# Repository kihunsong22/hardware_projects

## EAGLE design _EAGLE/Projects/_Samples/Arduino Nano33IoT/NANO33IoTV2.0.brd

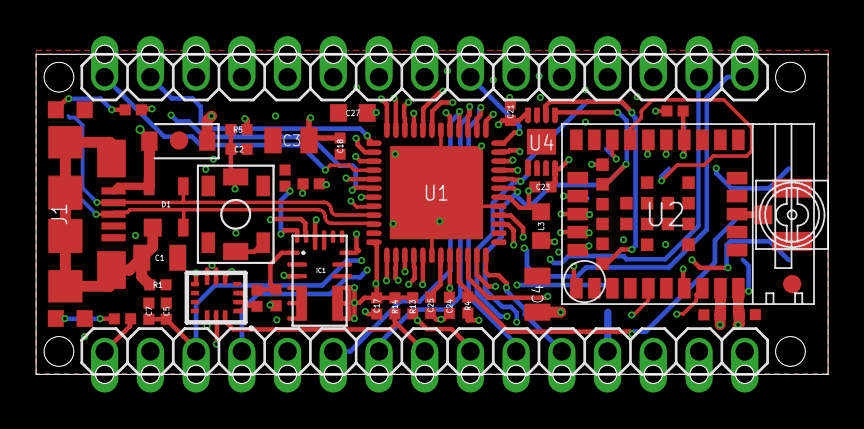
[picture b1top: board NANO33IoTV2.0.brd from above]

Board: 4 copper layers, 44.0 x 17.8 mm, 54 parts (1 on the bottom side), 51 nets.

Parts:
C1: 4n7; 0805-R2013X50N
C2, C7, C8, C9, C17, C18, C21, C23, C24: 100n; 0402-1005X55N
C3, C4: 22u; 0805-R2013X50N
C5: 4u7; 0402-1005X55N
C25: 1u; 0402-1005X55N
C27: 4u7; 0603-1608X90N
D1: PRTR5V; SOT190P230X110-4N
D2: PMEG6020; SODFL3517X110N
D+: DNP; TP-1.00MM
D-: DNP; TP-1.00MM
DL1: YELLOW; LEDC1608X80N-AK
DL2: GREEN; LEDC1608X80N-AK
FD1, FD2: DNP; FD-1-1.5
FRAME1: DNP; FRAME
IC1: MPM3610
J1: -; ZX62-AB-5PA
J3: DNP; U.FL-R-SMT-1(60)/NO_CREAM
J4: DNP; 2X03-TP1
JP2, JP3: 1X15-CASTELL
L3: BLM18PG471; 0603-1608X90N
PB1: PTS820; C&K_PTS820_NO_HOLES
R1: 1M; 0402-1005X55N
R2, R3: 330R; 0402-1005X55N
R4: 1k; 0402-1005X55N
R5, R7, R10: 100k; 0402-1005X55N
R6: 75k; 0402-1005X55N
R8: 24k; 0402-1005X55N
R9: 39k; 0402-1005X55N
R13, R14: 4k7; 0402-1005X55N
SJ1: DNP; SJ
TP_GPIO0: DNP; TP-0.8MM
TP_RST: DNP; TP-0.8MM
TP_RX: DNP; TP-0.8MM
TP_TX: DNP; TP-0.8MM
U1: D21G18; QFN50P700X700X90-49XN-EPSQ515
U2: NINA-W102; NINA-W1X
U3: LSM6DS3TR; LGA14L
U4: ECC608; SON50P300X200X60-9N-EP160X140
U$1: DNP; FRAME

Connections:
+3V3: C3.1, C8.1, C9.2, C17.1, C18.1, C21.1, C24.1, IC1.7, IC1.8, IC1.9, IC1.20, J4.1, JP2.2, L3.1, R2.2, R4.2, R5.2, R6.2, R7.2, R13.2, R14.2, U1.17, U1.36, U1.44, U2.9, U2.10, U3.5, U3.8, U3.12, U4.8
A0/DAC0: JP2.4, U1.3
A1: JP2.5, U1.47
A2: JP2.6, U1.16
A3: JP2.7, U1.15
A4/SDA: JP2.8, R14.1, U1.7, U2.35, U3.14, U4.5
A5/SCL: JP2.9, R13.1, U1.8, U2.31, U3.13, U4.6
A6: JP2.10, U1.14, U2.5
A7: JP2.11, U1.48, U2.8
AREF: C5.1, C7.1, JP2.3, U1.4
D2: JP3.5, U1.19
D3~: JP3.6, U1.20
D4: JP3.7, U1.12
D5~: JP3.8, U1.10
D6~: JP3.9, U1.9
D7: JP3.10, U1.11
D8: JP3.11, U1.27
D9~: JP3.12, U1.29
D10~: JP3.13, U1.30
GND: C1.2, C2.2, C3.2, C4.2, C5.2, C7.2, C8.2, C9.1, C17.2, C18.2, C21.2, C23.2, C24.2, C25.2, C27.2, DL1.C, DL2.C, IC1.3, IC1.12, IC1.13, IC1.14, J1.5, J3.GND1, J3.GND2, J4.5, JP2.14, JP3.4, PB1.1, PB1.2, PB1.3, PB1.4, PB1.5, R1.1, R8.1, R9.1, U1.5, U1.18, U1.35, U1.42, U1.49, U2.6, U2.12, U2.14, U2.26, U2.30, U2.GND@1, U2.GND@2, U2.GND@3, U2.GND@4, U2.GND@5, U2.GND@6, U2.GND@7, U2.GND@8, U2.GND@9, U2.GND@10, U2.GND@11, U2.GND@12, U3.1, U3.2, U3.3, U3.6, U3.7, U4.4
MISO~: JP3.15, U1.28
MOSI: JP3.14, U1.25
N17852357: C23.1, C27.1, L3.2, U1.6
N17852431: C25.1, U1.43
unnamed: C1.1, D1.1, J1.6, J1.7, J1.8, J1.9, J1.10, J1.11, R1.2
unnamed: DL2.A, R2.1
unnamed: DL1.A, R3.1
unnamed: J3.SIG, U2.13
unnamed: IC1.1, R6.1, R8.2
unnamed: IC1.18, R9.2
unnamed: IC1.17, R10.1
unnamed: JP2.12, SJ1.2
PA12_S2_TX/MOSI: U1.21, U2.36
PA13_S2_RX/MISO: U1.22, U2.1
PA14_S2_RTS/CS: U1.23, U2.21, U2.28
PA15_S2_CTS/SCK: U1.24, U2.20, U2.29
PA27_GPIO0: TP_GPIO0.X, U1.39, U2.27
PA28_ACK: U1.41, U2.7
PA30_SWCLK: J4.3, R4.1, U1.45
PA31_SWDIO: J4.2, U1.46
RESETN: C2.1, J4.6, JP2.13, JP3.3, PB1.6, R5.1, U1.40
RSTN_NINA: R7.1, TP_RST.X, U1.13, U2.19
RX: JP3.2, U1.38
RX_NINA_PROG: TP_RX.X, U1.32, U2.22
SCK: JP2.1, R3.2, U1.26
TX: JP3.1, U1.37
TX_NINA_PROG: TP_TX.X, U1.31, U2.23
USB_N: D1.3, D-.X, J1.2, U1.33
USB_P: D1.2, D+.X, J1.3, U1.34
VIN: C4.1, D2.C, IC1.16, JP2.15, R10.2
VUSB: D1.4, D2.A, J1.1, SJ1.1

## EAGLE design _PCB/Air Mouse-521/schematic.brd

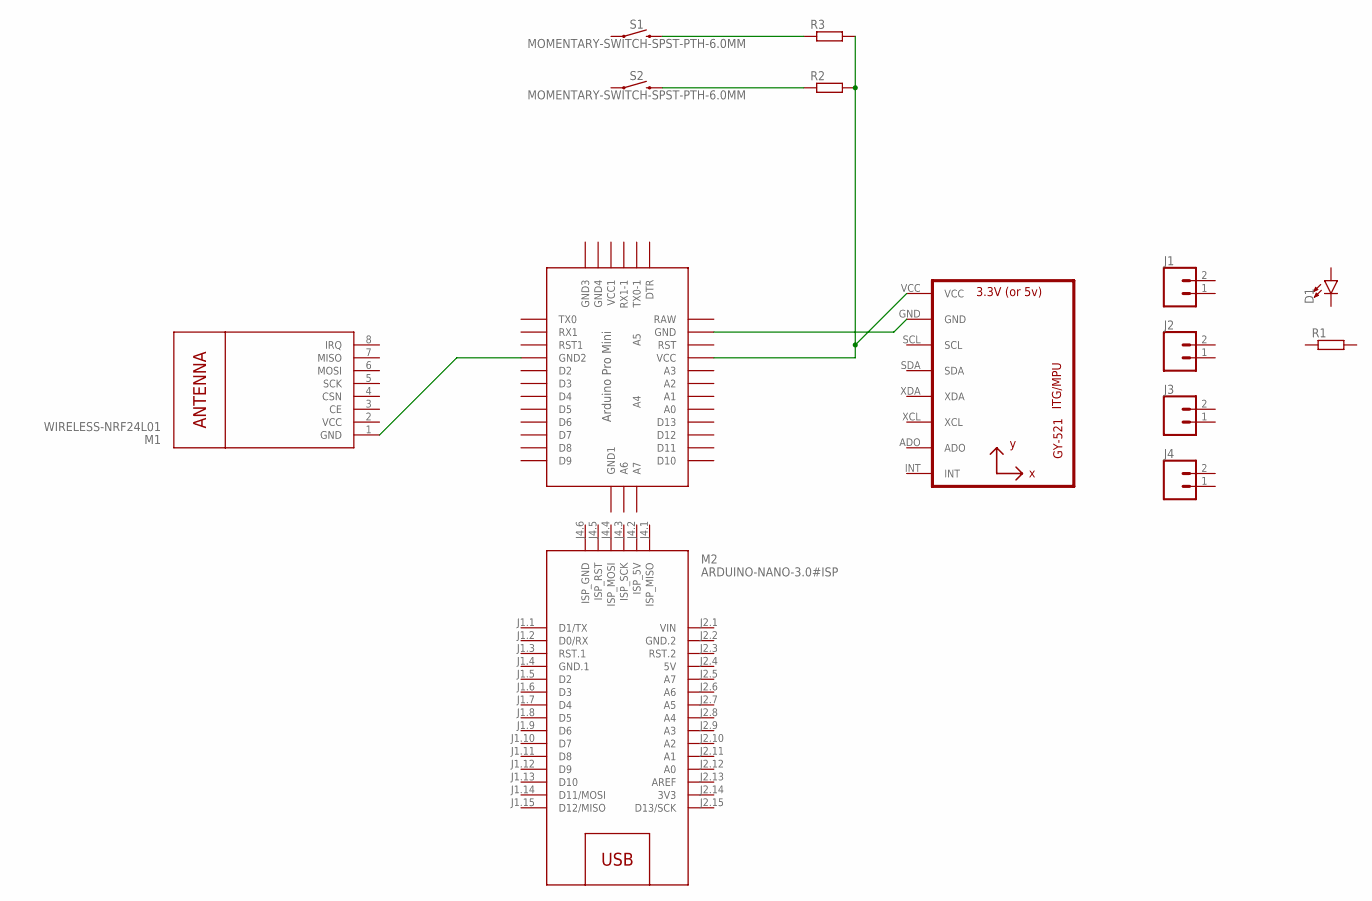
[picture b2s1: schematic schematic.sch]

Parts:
D1: LED3MM; LED_3MM
J1, J2, J3, J4: CONN_02LOCK; 1X02_LOCK
M1: WIRELESS-NRF24L01
M2: ARDUINO-NANO-3.0#ISP
R1, R2, R3: R-EU_0207/10; 0207/10
S1, S2: MOMENTARY-SWITCH-SPST-PTH-6.0MM; TACTILE_SWITCH_PTH_6.0MM
U1: GY-521MPU6050; GY-521
U$1: ABK-PRO-MINI

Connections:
3V3: M2.J2.14 (3V3)
5V: M2.J2.4 (5V)
GND.1: M2.J1.4 (GND.1)
GND.2: M2.J2.2 (GND.2)
unnamed: R3.1, S1.3 (2)
unnamed: R2.1, S2.3 (2)
unnamed: R2.2, R3.2, U1.VCC, U$1.VCC
unnamed: U1.GND, U$1.GND
unnamed: M1.1 (GND), U$1.GND1 (GND2)
VCC: M1.2 (VCC)
VIN: M2.J2.1 (VIN)

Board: 2 copper layers, 14 parts (0 on the bottom side), 5 nets, no tracks yet.

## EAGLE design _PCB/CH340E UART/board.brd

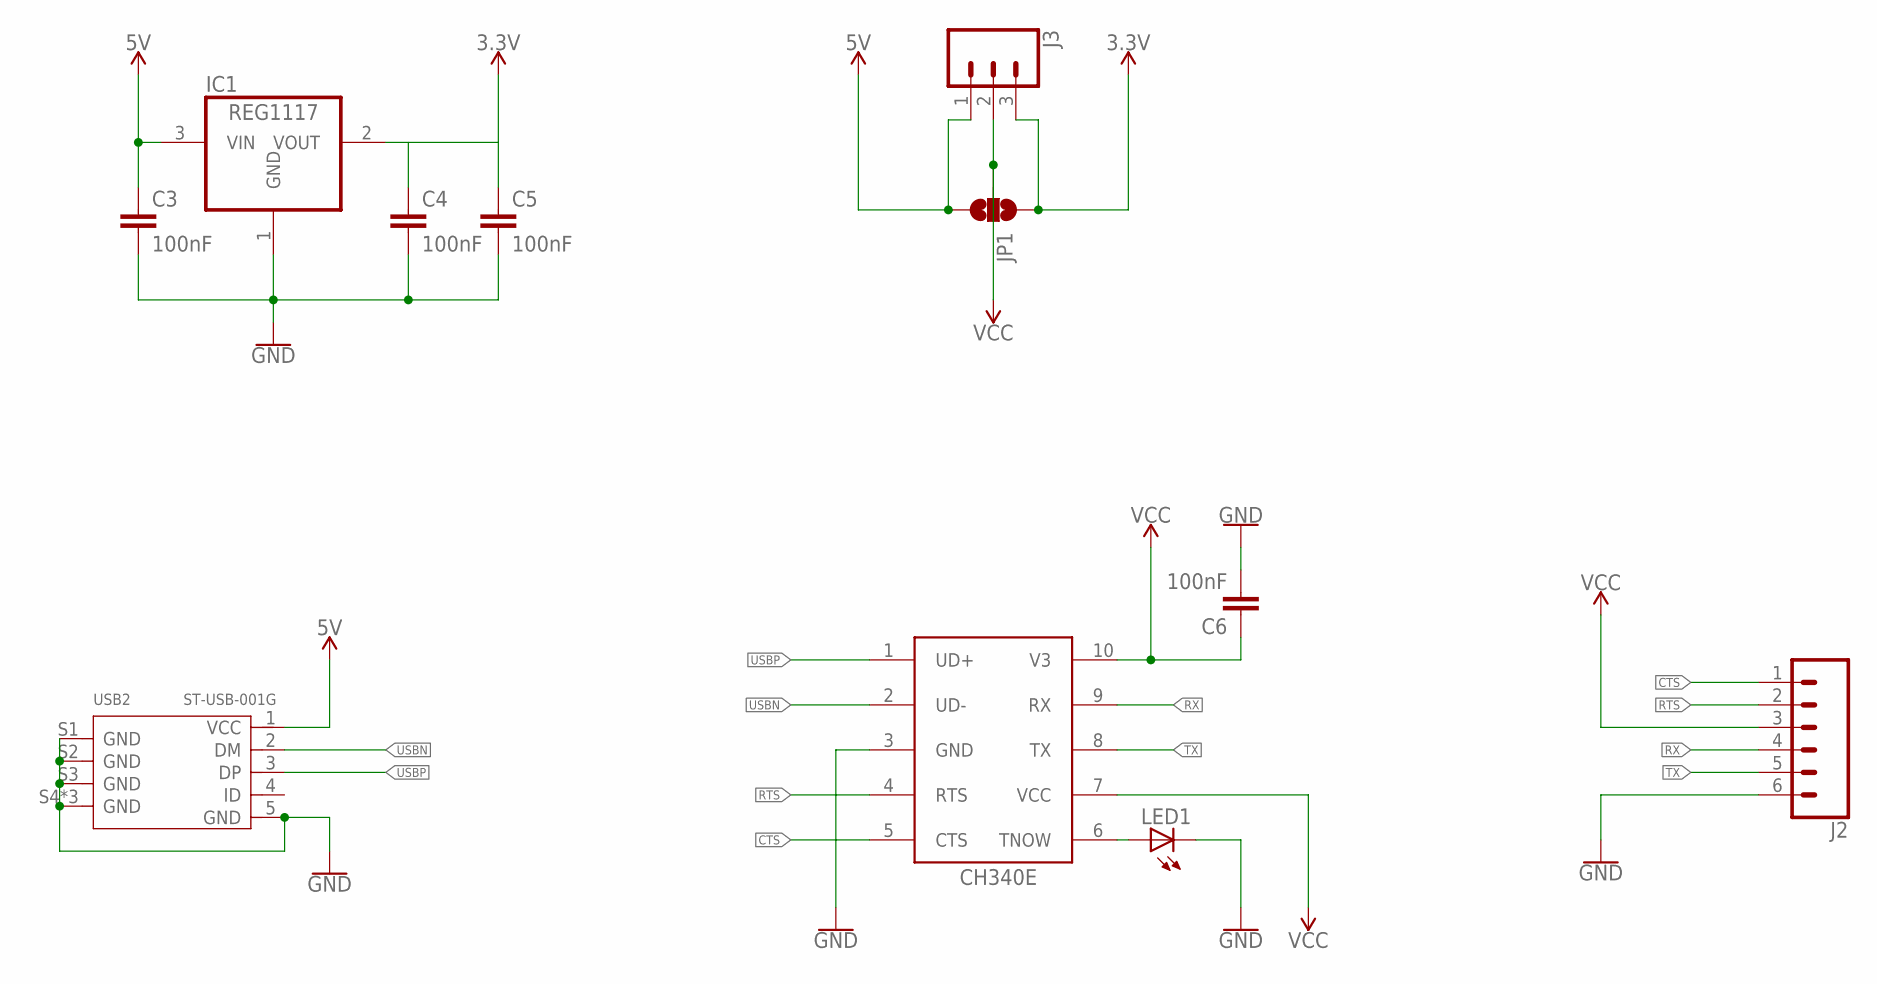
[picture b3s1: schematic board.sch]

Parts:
C3, C4, C5, C6: 100nF; C0805
CH340E: CH340ESMD; MSOP10
IC1: REG1117; SOT223
J2: CONN_06SILK_FEMALE_PTH; 1X06
J3: CONN_03; 1X03
JP1: JUMPER-SMT_3_NO_SILK; SMT-JUMPER_3_NO_SILK
LED1: LEDCHIPLED_0805; CHIPLED_0805
USB2: ST-USB-001G; MICRO-USB5+4P-SMD-0.65-B

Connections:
3.3V: J3.3, JP1.1
3V3: C4.1, C5.1, IC1.2 (VOUT)
5V: C3.1, IC1.3 (VIN), J3.1, JP1.3, USB2.1 (VCC)
CTS: CH340E.5 (CTS), J2.1
GND: C3.2, C4.2, C5.2, C6.2, CH340E.3 (GND), IC1.1 (GND), J2.6, LED1.C, USB2.5 (GND), USB2.S1 (GND), USB2.S2 (GND), USB2.S3 (GND), USB2.S4 (GND), USB2.S5 (GND), USB2.S6 (GND)
unnamed: CH340E.6 (TNOW), LED1.A
RTS: CH340E.4 (RTS), J2.2
RX: CH340E.9 (RX), J2.4
TX: CH340E.8 (TX), J2.5
USBN: CH340E.2 (UD-), USB2.2 (DM)
USBP: CH340E.1 (UD+), USB2.3 (DP)
VCC: C6.1, CH340E.7 (VCC), CH340E.10 (V3), J2.3, J3.2, JP1.2

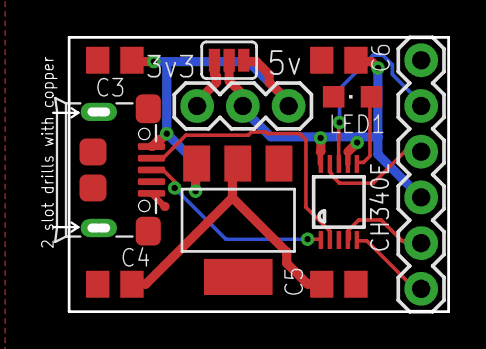
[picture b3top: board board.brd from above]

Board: 2 copper layers, 22.0 x 15.2 mm, 11 parts (0 on the bottom side), 12 nets.

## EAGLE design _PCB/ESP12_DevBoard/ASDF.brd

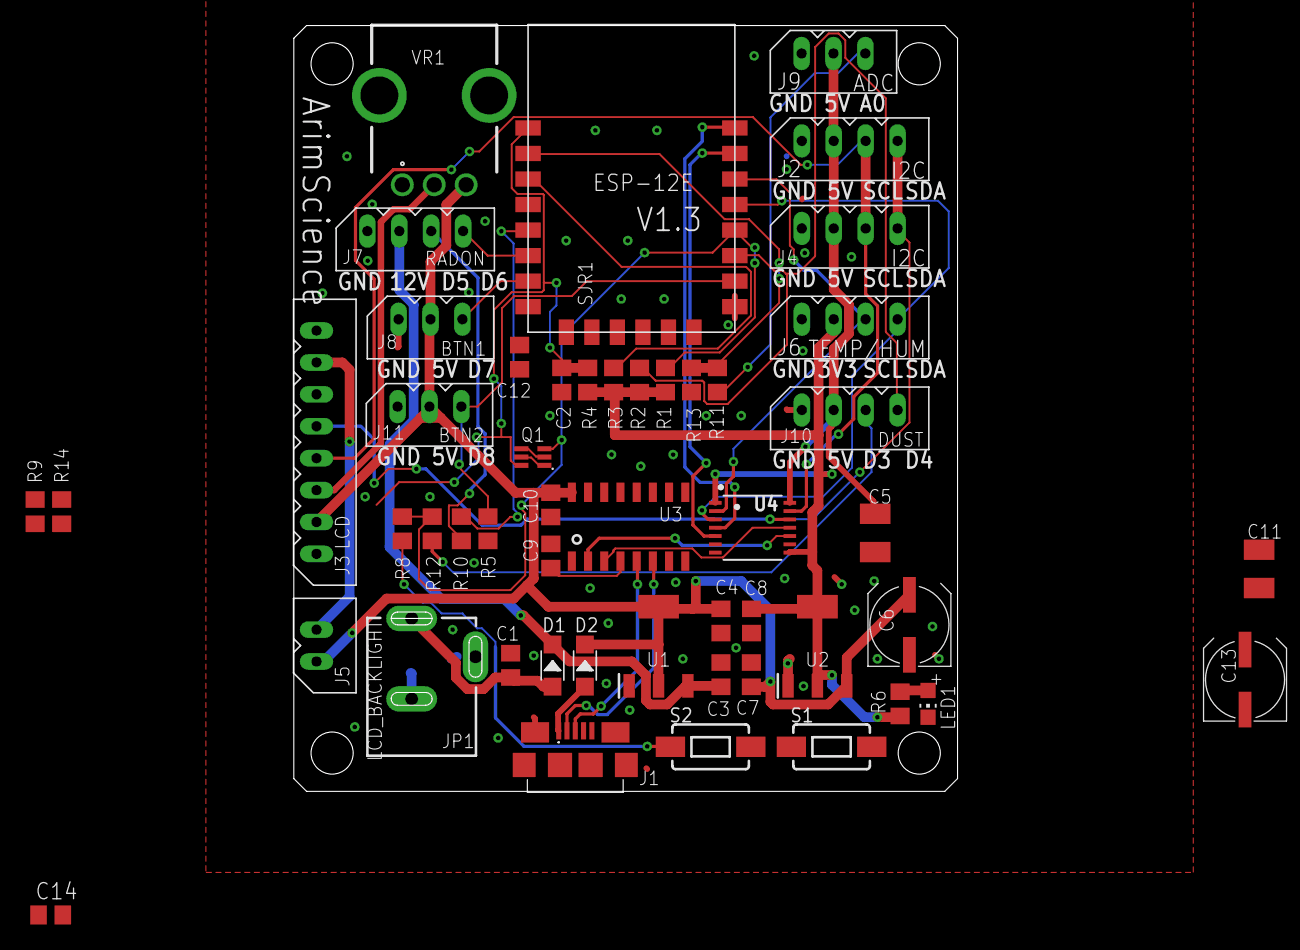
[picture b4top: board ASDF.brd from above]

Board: 2 copper layers, 52.0 x 60.0 mm, 51 parts (0 on the bottom side), 37 nets.

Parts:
C1, C3, C7: 10uF; C0805
C2, C9, C10, C12, C14: 100nF; C0805
C4, C8: 22uF; C0805
C5, C11: 100uF; SMC_B
C6, C13: 220uF; UD-6,3X7,7_NICHICON
D1, D2: 1N5819W; SOD-123
J1: ZX62-B-5PA(33); ZX62B5PA33
J2, J4: I2C; 5267-4
J3: LCD; 5267-8
J5: LCD_BACKLIGHT; 5267-2
J6: TEMP/HUM; 5267-4
J7: RADON; 5267-4
J8: BTN1; 5267-3
J9: ADC; 5267-3
J10: DUST; 5267-4
J11: BTN2; 5267-3
JP1: POWER_JACKSLT; POWER_JACK_SLOT
LED1: green; CHIP-LED0805
Q1: UMH3N; SOT65P210X100-6N
R1, R2, R3, R4, R5, R6, R9, R14: 10k; R0805
R8, R10, R12: 470Ω; R0805
R11: 47k(1%); R0805
R13: 10k(1%); R0805
S1: RST; TACTILE_SWITCH_SMD_6.0X3.5MM
S2: FLASH; TACTILE_SWITCH_SMD_6.0X3.5MM
SJR1: ESP-12E; ESP8266-ESP12E
U1: 5V_REG; SOT230P700X170-4N
U2: 3V3_REG; SOT230P700X170-4N
U3: CH340C; SOIC16
U4: TXB0104; TSSOP14
VR1: RK09K1130AAU; RK09K1130BGM

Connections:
3.3V: C8.2, C11.+, C12.2, C13.+, J6.P$2, R1.1, R2.1, R3.1, R4.1, R6.1, SJR1.8, U2.2, U2.4, U4.1, U4.8
5V: C4.1, C5.+, C6.+, C7.1, C10.2, C14.2, D2.-, J2.P$2, J3.P$2, J4.P$2, J5.P$1, J8.P$2, J9.P$2, J10.P$2, J11.P$2, U1.2, U1.4, U2.3, U3.16, U4.14, VR1.3
5V_INPUT: D2.+, J1.VCC
12V: C3.1, D1.-, J7.P$2, U1.3
ADC: R11.1, R13.2, SJR1.2
D+_USB: J1.D+, U3.5
D-_USB: J1.D-, U3.6
DTR: Q1.2, Q1.4, R9.1
EN: R3.2, SJR1.3
GND: C1.1, C2.1, C3.2, C4.2, C5.-, C6.-, C7.2, C8.1, C9.1, C10.1, C11.-, C12.1, C13.-, C14.1, J1.GND, J1.SHIELD_1, J1.SHIELD_2, J1.SHIELD_3, J1.SHIELD_4, J1.SHIELD_5, J1.SHIELD_6, J2.P$1, J3.P$1, J3.P$8, J4.P$1, J6.P$1, J7.P$1, J8.P$1, J9.P$1, J10.P$1, J11.P$1, JP1.GND@1, JP1.GND@2, LED1.C, R5.1, R13.1, S1.2, S2.2, SJR1.9, U1.1, U2.1, U3.1, U4.7, VR1.1
GPIO0: Q1.3, R1.2, R8.1, R12.1, SJR1.12
GPIO2: J10.P$4, R2.2, SJR1.11
GPIO4: J6.P$4, SJR1.13, U4.3
GPIO5: J6.P$3, SJR1.14, U4.2
GPIO12: J7.P$4, SJR1.6
GPIO13: J8.P$3, SJR1.7
GPIO14: R10.1, SJR1.5
GPIO15: J11.P$3, R5.2, SJR1.10
LED+: J3.P$7, J5.P$2
unnamed: C9.2, U3.4
unnamed: J3.P$3, VR1.2
unnamed: C1.2, D1.+, JP1.PWR
unnamed: LED1.A, R6.2
unnamed: J9.P$3, R11.2
unnamed: J7.P$3, R10.2
unnamed: R9.2, U3.13
unnamed: R14.2, U3.14
unnamed: J10.P$3, R12.2
POWER1: R8.2, S2.1
RST: C2.2, Q1.6, R4.2, S1.1, SJR1.1
RTS: Q1.1, Q1.5, R14.1
RXD: SJR1.15, U4.5
RXD_5V: U3.2, U4.10
SCL_5V: J2.P$3, J3.P$4, J4.P$3, U4.13
SDA_5V: J2.P$4, J3.P$5, J4.P$4, U4.12
TXD: SJR1.16, U4.4
TXD_5V: U3.3, U4.11

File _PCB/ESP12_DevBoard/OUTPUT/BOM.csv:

Qty,Designator,Value,Package,MANUFACTURER_NAME,MANUFACTURER_PART_NUMBER
1,J5,2,,MOLEX,22035025
3,"J8, J9, J11",3,,MOLEX,22035035
5,"J2, J4, J6, J7, J10",4,,MOLEX,99990988
1,J3,8,,MOLEX,99990992
1,U1,5V regulator,SOT-223,Diodes Incorporated,AZ1117H-5.0TRE1
1,U2,3.3V regulator,SOT-223,Diodes Incorporated,AZ1117H-3.3TRG1
3,"C1, C3, C7",10uF,C0805,Samsung Electro-Mechanics,CL21A106KAYNNNE
4,"C2, C9, C10, C12",100nF,C0805,Samsung Electro-Mechanics,CL21F104ZBCNNNC
2,"C4, C8",22uF,C0805,Samsung Electro-Mechanics,CL21A226MAQNNNF
1,U3,CH340C,SOP-16_150mil,Jiangsu Qin Heng,CH340C
2,"C5, C11",100uF,SMC_B,AVX,TAJB107M010RNJ
1,C6,220uF,6.3*7.7mm,ROQANG,VT1E101M0607
1,SJR1,ESP-12E,ESP8266-ESP12E,AI-Thinker,ESP-12E
1,LED1,green,LED0805,Orient,ORH-G35A
2,"S1, S2",pushbutton,6.0*3.5mm,HYP (Hongyuan Precision),1TS002B-2300-5000-CT
1,JP1,5.5*2.1mm,14.0*9.0mm,Korean Hroparts Elec,DC-005-20A
1,VR1,10k,RK09K1130BGM,ALPS Electric,RK09K1130AAU
6,"R1, R2, R3, R4, R5, R13",10k,R0805,Uniroyal Elec,0805W8F1002T5E
1,R11,47k(1%),R0805,Uniroyal Elec,0805W8F4702T5E
5,"R6, R7, R8, R10, R12",470,R0805,Guangdong Fenghua Advanced Tech,RS-05K471JT
2,"D1, D2",1N5819W,SOD-123F,Shandong Jingdao Microelectronics,1N5819W
1,U4,TXB0104,TSSOP14,Texas Instruments,TXB0104PWR
1,Q1,UMH3N,SOT65P210X100-6N,Changjiang Electronics Tech,UMH3N
1,J1,ZX62-B-5PA(33),ZX62B5PA33,Hirose,ZX62-B-5PA(33)

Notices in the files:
_EAGLE/Projects/_Samples/Arduino Nano33IoT/NANO33IoTV2.0.brd:
Copyright (c) 2016-2017 Arduino LLC.  All right reserved. EAGLE Design Rules
parts and their libraries:
SparkFun-Connectors: Licensing: Creative Commons ShareAlike 4.0 International - https://creativecommons.org/licenses/by-sa/4.0
Arduino-utility: This work is licensed under a Creative Commons Attribution-ShareAlike 4.0 International License.
